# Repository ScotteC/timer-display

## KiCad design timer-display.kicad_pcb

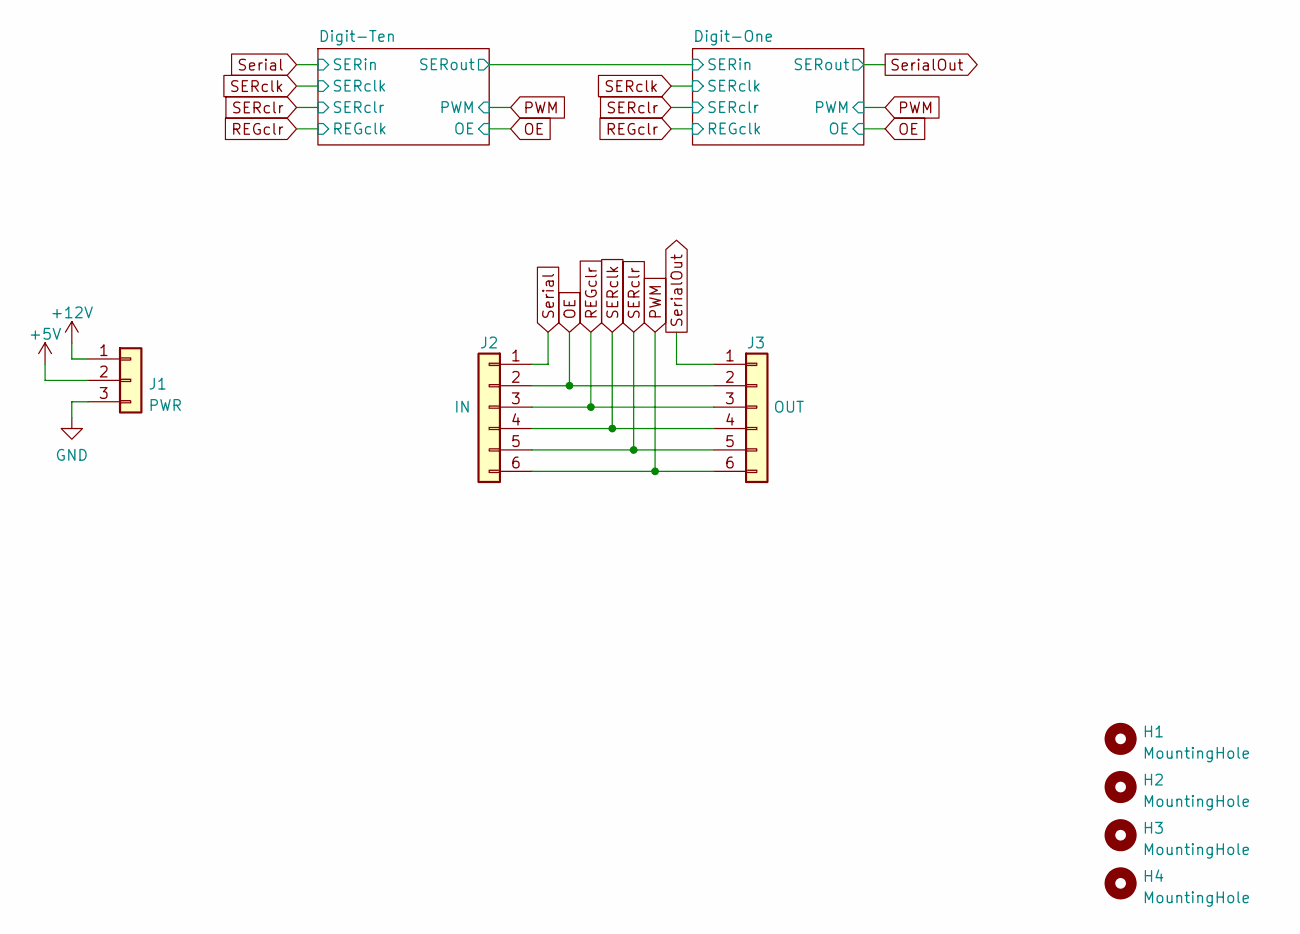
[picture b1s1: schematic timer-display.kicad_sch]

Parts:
H1, H2, H3, H4: MountingHole; MountingHole_3.2mm_M3
J1: PWR; PinSocket_1x03_P2.54mm_Vertical
J2: IN; PinSocket_1x06_P1.27mm_Vertical
J3: OUT; PinSocket_1x06_P1.27mm_Vertical

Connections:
+5V: J1.2; also elsewhere on the board
+12V: J1.1; also elsewhere on the board
GND: J1.3; also elsewhere on the board
OE: J2.2, J3.2; also elsewhere on the board
PWM: J2.6, J3.6; also elsewhere on the board
REGclr: J2.3, J3.3; also elsewhere on the board
SERclk: J2.4, J3.4; also elsewhere on the board
SERclr: J2.5, J3.5; also elsewhere on the board
Serial: J2.1; also elsewhere on the board
SerialOut: J3.1; also elsewhere on the board

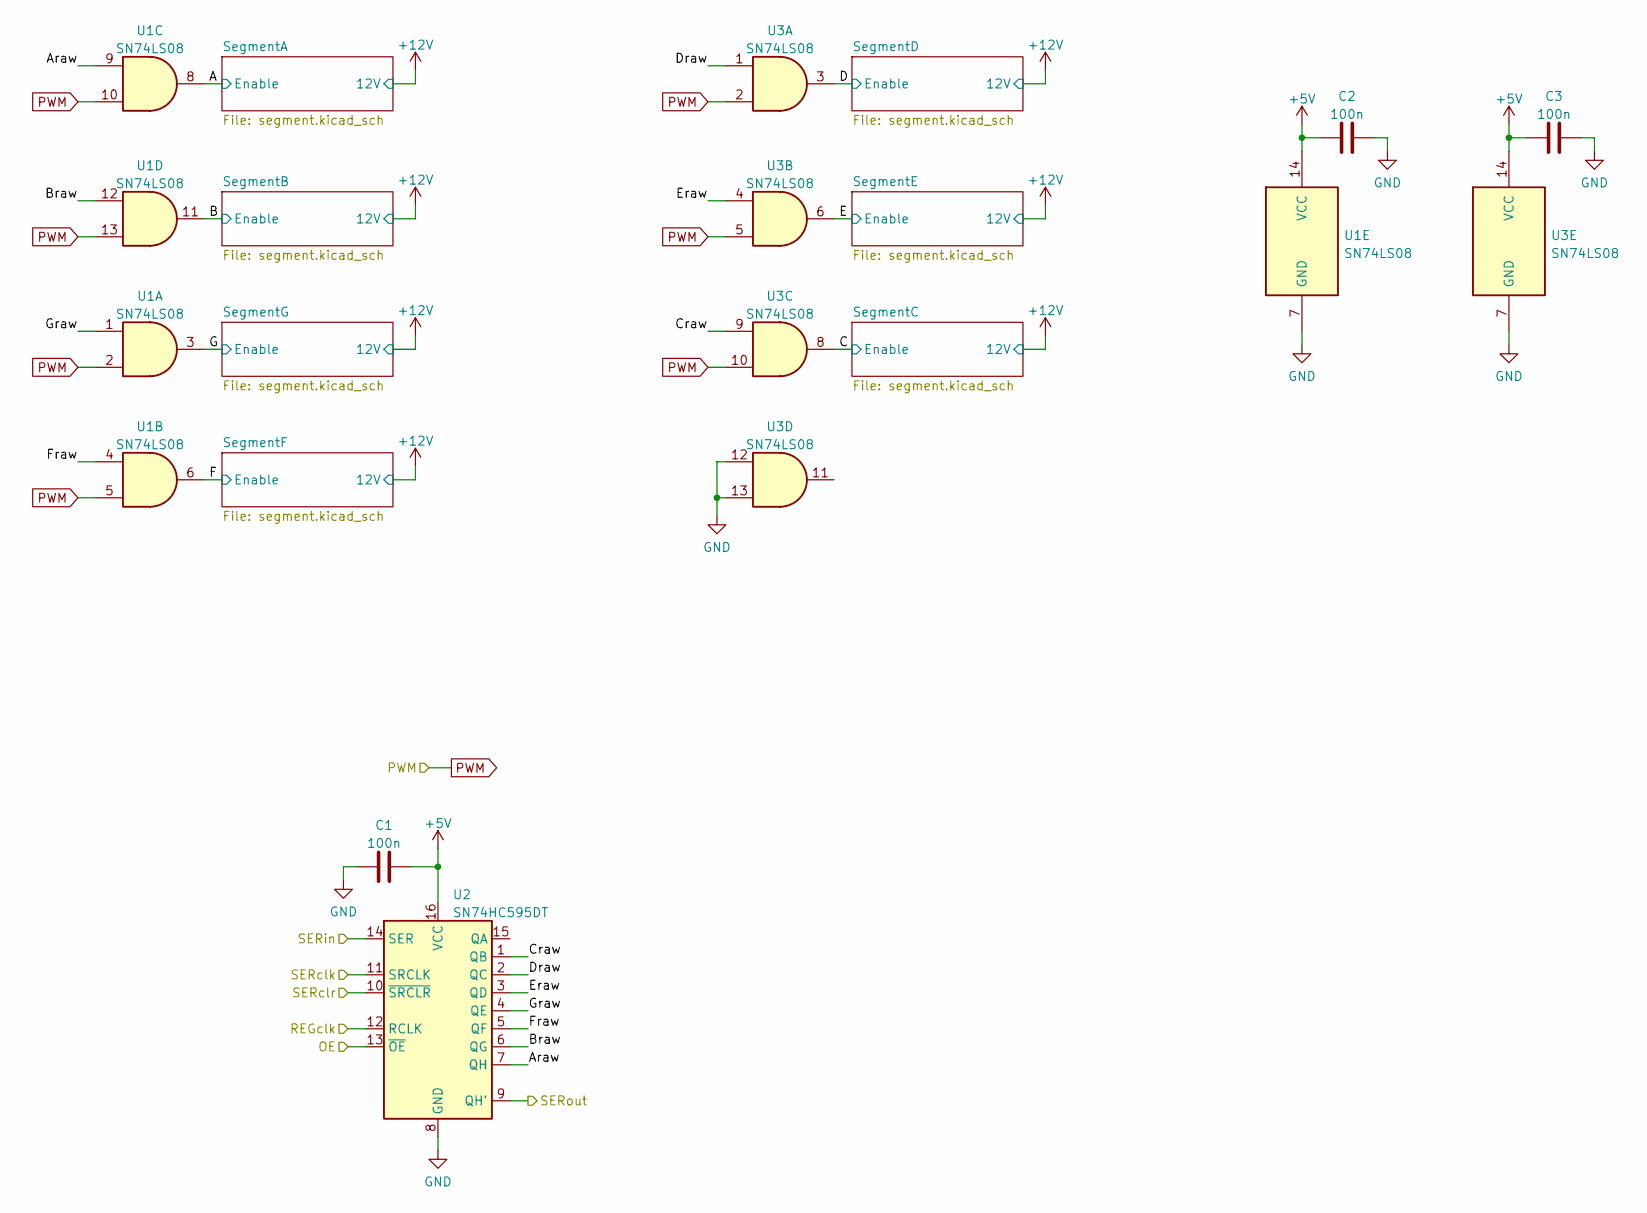
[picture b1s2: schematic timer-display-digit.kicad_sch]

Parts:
C1, C2, C3: 100n; C_0603_1608Metric
U1, U3: SN74LS08; SOIC-14_3.9x8.7mm_P1.27mm; Mouser# 595-SN74LS08DR
U2: SN74HC595DT; SOIC-16_3.9x9.9mm_P1.27mm; Mouser# 595-SN74HC595DT

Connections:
+5V: C1.1, C2.1, C3.1, U1.14 (VCC), U2.16 (VCC), U3.14 (VCC); also elsewhere on the board
/Digit-One/SERin: U2.9 (QH'); also elsewhere on the board
/Digit-Ten/A: U1.8; also elsewhere on the board
/Digit-Ten/Araw: U1.9, U2.7 (QH)
/Digit-Ten/B: U1.11; also elsewhere on the board
/Digit-Ten/Braw: U1.12, U2.6 (QG)
/Digit-Ten/C: U3.8; also elsewhere on the board
/Digit-Ten/Craw: U2.1 (QB), U3.9
/Digit-Ten/D: U3.3; also elsewhere on the board
/Digit-Ten/Draw: U2.2 (QC), U3.1
/Digit-Ten/E: U3.6; also elsewhere on the board
/Digit-Ten/Eraw: U2.3 (QD), U3.4
/Digit-Ten/F: U1.6; also elsewhere on the board
/Digit-Ten/Fraw: U1.4, U2.5 (QF)
/Digit-Ten/G: U1.3; also elsewhere on the board
/Digit-Ten/Graw: U1.1, U2.4 (QE)
GND: C1.2, C2.2, C3.2, U1.7 (GND), U2.8 (GND), U3.7 (GND), U3.12, U3.13; also elsewhere on the board
OE: U2.13 (~OE); also elsewhere on the board
PWM: U1.2, U1.5, U1.10, U1.13, U3.2, U3.5, U3.10; also elsewhere on the board
REGclr: U2.12 (RCLK); also elsewhere on the board
SERclk: U2.11 (SRCLK); also elsewhere on the board
SERclr: U2.10 (~SRCLR); also elsewhere on the board
Serial: U2.14 (SER); also elsewhere on the board

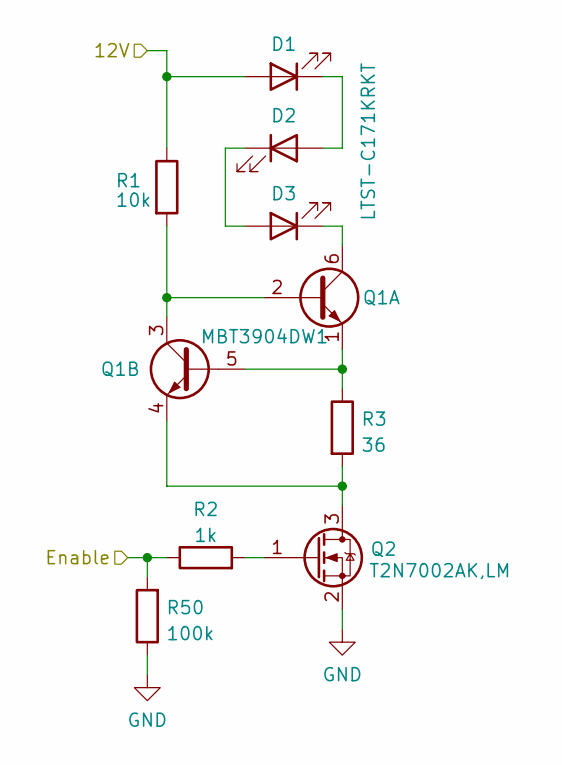
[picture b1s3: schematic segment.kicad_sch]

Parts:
D1, D2, D3: LTST-C171KRKT; LED_0805_2012Metric; Mouser# 859-LTST-C171KRKT
Q1: MBT3904DW1; SOT-363_SC-70-6; Mouser# 863-MBT3904DW1T3G
Q2: T2N7002AK,LM; SOT-23; Mouser# 757-T2N7002AKLM
R1: 10k; R_0603_1608Metric
R2: 1k; R_0603_1608Metric; Mouser# 791-RMC1/16-100JTP
R3: 36; R_0603_1608Metric; Mouser# 603-RC0603FR-0736RL
R50: 100k; R_0603_1608Metric; Mouser# 791-RMC1/16-100JTP

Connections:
+12V: D1.2 (A), R1.1; also elsewhere on the board
/Digit-Ten/A: R2.1, R50.2; also elsewhere on the board
GND: Q2.2 (S), R50.1; also elsewhere on the board
unnamed: D1.1 (K), D2.2 (A)
unnamed: D2.1 (K), D3.2 (A)
unnamed: D3.1 (K), Q1.6 (C1)
unnamed: Q1.1 (E1), Q1.5 (B2), R3.1
unnamed: Q1.2 (B1), Q1.3 (C2), R1.2
unnamed: Q1.4 (E2), Q2.3 (D), R3.2
unnamed: Q2.1 (G), R2.2

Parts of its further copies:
D4, D5, D6, D7, D8, D9, D10, D11, D12, D13, D14, D15, D16, D17, D18, D19, D20, D21, D22, D23, D24, D25, D26, D27, D28, D29, D30, D31, D32, D33, D34, D35, D36, D37, D38, D39, D40, D41, D42: LTST-C171KRKT; LED_0805_2012Metric; Mouser# 859-LTST-C171KRKT
Q3, Q5, Q7, Q9, Q11, Q13, Q15, Q17, Q19, Q21, Q23, Q25, Q27: MBT3904DW1; SOT-363_SC-70-6; Mouser# 863-MBT3904DW1T3G
Q4, Q6, Q8, Q10, Q12, Q14, Q16, Q18, Q20, Q22, Q24, Q26, Q28: T2N7002AK,LM; SOT-23; Mouser# 757-T2N7002AKLM
R4, R7, R10, R13, R16, R19, R22, R25, R28, R31, R34, R37, R40: 10k; R_0603_1608Metric
R5, R8, R11, R14, R17, R20, R23, R26, R29, R32, R35, R38, R41: 1k; R_0603_1608Metric; Mouser# 791-RMC1/16-100JTP
R6, R9, R12, R15, R18, R21, R24, R27, R30, R33, R36, R39, R42: 36; R_0603_1608Metric; Mouser# 603-RC0603FR-0736RL
R43, R44, R45, R46, R47, R48, R49, R51, R52, R53, R54, R55, R56: 100k; R_0603_1608Metric; Mouser# 791-RMC1/16-100JTP

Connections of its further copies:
+12V: D4.2 (A), D7.2 (A), D10.2 (A), D13.2 (A), D16.2 (A), D19.2 (A), D22.2 (A), D25.2 (A), D28.2 (A), D31.2 (A), D34.2 (A), D37.2 (A), D40.2 (A), R4.1, R7.1, R10.1, R13.1, R16.1, R19.1, R22.1, R25.1, R28.1, R31.1, R34.1, R37.1, R40.1; also elsewhere on the board
/Digit-One/A: R29.1, R45.2; also elsewhere on the board
/Digit-One/B: R32.1, R46.2; also elsewhere on the board
/Digit-One/C: R38.1, R48.2; also elsewhere on the board
/Digit-One/D: R35.1, R47.2; also elsewhere on the board
/Digit-One/E: R41.1, R49.2; also elsewhere on the board
/Digit-One/F: R23.1, R43.2; also elsewhere on the board
/Digit-One/G: R26.1, R44.2; also elsewhere on the board
/Digit-Ten/B: R5.1, R51.2; also elsewhere on the board
/Digit-Ten/C: R8.1, R56.2; also elsewhere on the board
/Digit-Ten/D: R11.1, R54.2; also elsewhere on the board
/Digit-Ten/E: R14.1, R55.2; also elsewhere on the board
/Digit-Ten/F: R17.1, R53.2; also elsewhere on the board
/Digit-Ten/G: R20.1, R52.2; also elsewhere on the board
GND: Q4.2 (S), Q6.2 (S), Q8.2 (S), Q10.2 (S), Q12.2 (S), Q14.2 (S), Q16.2 (S), Q18.2 (S), Q20.2 (S), Q22.2 (S), Q24.2 (S), Q26.2 (S), Q28.2 (S), R43.1, R44.1, R45.1, R46.1, R47.1, R48.1, R49.1, R51.1, R52.1, R53.1, R54.1, R55.1, R56.1; also elsewhere on the board
unnamed: D4.1 (K), D5.2 (A)
unnamed: D5.1 (K), D6.2 (A)
unnamed: D6.1 (K), Q3.6 (C1)
unnamed: D7.1 (K), D8.2 (A)
unnamed: D8.1 (K), D9.2 (A)
unnamed: D9.1 (K), Q5.6 (C1)
unnamed: D10.1 (K), D11.2 (A)
unnamed: D11.1 (K), D12.2 (A)
unnamed: D12.1 (K), Q7.6 (C1)
unnamed: D13.1 (K), D14.2 (A)
unnamed: D14.1 (K), D15.2 (A)
unnamed: D15.1 (K), Q9.6 (C1)
unnamed: D16.1 (K), D17.2 (A)
unnamed: D17.1 (K), D18.2 (A)
unnamed: D18.1 (K), Q11.6 (C1)
unnamed: D19.1 (K), D20.2 (A)
unnamed: D20.1 (K), D21.2 (A)
unnamed: D21.1 (K), Q13.6 (C1)
unnamed: D22.1 (K), D23.2 (A)
unnamed: D23.1 (K), D24.2 (A)
unnamed: D24.1 (K), Q15.6 (C1)
unnamed: D25.1 (K), D26.2 (A)
unnamed: D26.1 (K), D27.2 (A)
unnamed: D27.1 (K), Q17.6 (C1)
unnamed: D28.1 (K), D29.2 (A)
unnamed: D29.1 (K), D30.2 (A)
unnamed: D30.1 (K), Q19.6 (C1)
unnamed: D31.1 (K), D32.2 (A)
unnamed: D32.1 (K), D33.2 (A)
unnamed: D33.1 (K), Q21.6 (C1)
unnamed: D34.1 (K), D35.2 (A)
unnamed: D35.1 (K), D36.2 (A)
unnamed: D36.1 (K), Q23.6 (C1)
unnamed: D37.1 (K), D38.2 (A)
unnamed: D38.1 (K), D39.2 (A)
unnamed: D39.1 (K), Q25.6 (C1)
unnamed: D40.1 (K), D41.2 (A)
unnamed: D41.1 (K), D42.2 (A)
unnamed: D42.1 (K), Q27.6 (C1)
unnamed: Q3.1 (E1), Q3.5 (B2), R6.1
unnamed: Q3.2 (B1), Q3.3 (C2), R4.2
unnamed: Q3.4 (E2), Q4.3 (D), R6.2
unnamed: Q4.1 (G), R5.2
unnamed: Q5.1 (E1), Q5.5 (B2), R9.1
unnamed: Q5.2 (B1), Q5.3 (C2), R7.2
unnamed: Q5.4 (E2), Q6.3 (D), R9.2
unnamed: Q6.1 (G), R8.2
unnamed: Q7.1 (E1), Q7.5 (B2), R12.1
unnamed: Q7.2 (B1), Q7.3 (C2), R10.2
unnamed: Q7.4 (E2), Q8.3 (D), R12.2
unnamed: Q8.1 (G), R11.2
unnamed: Q9.1 (E1), Q9.5 (B2), R15.1
unnamed: Q9.2 (B1), Q9.3 (C2), R13.2
unnamed: Q10.1 (G), R14.2
unnamed: Q9.4 (E2), Q10.3 (D), R15.2
unnamed: Q11.1 (E1), Q11.5 (B2), R18.1
unnamed: Q11.2 (B1), Q11.3 (C2), R16.2
unnamed: Q11.4 (E2), Q12.3 (D), R18.2
unnamed: Q12.1 (G), R17.2
unnamed: Q13.1 (E1), Q13.5 (B2), R21.1
unnamed: Q13.2 (B1), Q13.3 (C2), R19.2
unnamed: Q13.4 (E2), Q14.3 (D), R21.2
unnamed: Q14.1 (G), R20.2
unnamed: Q15.1 (E1), Q15.5 (B2), R24.1
unnamed: Q15.2 (B1), Q15.3 (C2), R22.2
unnamed: Q15.4 (E2), Q16.3 (D), R24.2
unnamed: Q16.1 (G), R23.2
unnamed: Q17.1 (E1), Q17.5 (B2), R27.1
unnamed: Q17.2 (B1), Q17.3 (C2), R25.2
unnamed: Q17.4 (E2), Q18.3 (D), R27.2
unnamed: Q18.1 (G), R26.2
unnamed: Q19.1 (E1), Q19.5 (B2), R30.1
unnamed: Q19.2 (B1), Q19.3 (C2), R28.2
unnamed: Q19.4 (E2), Q20.3 (D), R30.2
unnamed: Q20.1 (G), R29.2
unnamed: Q21.1 (E1), Q21.5 (B2), R33.1
unnamed: Q21.2 (B1), Q21.3 (C2), R31.2
unnamed: Q21.4 (E2), Q22.3 (D), R33.2
unnamed: Q22.1 (G), R32.2
unnamed: Q23.1 (E1), Q23.5 (B2), R36.1
unnamed: Q23.2 (B1), Q23.3 (C2), R34.2
unnamed: Q23.4 (E2), Q24.3 (D), R36.2
unnamed: Q24.1 (G), R35.2
unnamed: Q25.1 (E1), Q25.5 (B2), R39.1
unnamed: Q25.2 (B1), Q25.3 (C2), R37.2
unnamed: Q25.4 (E2), Q26.3 (D), R39.2
unnamed: Q26.1 (G), R38.2
unnamed: Q27.1 (E1), Q27.5 (B2), R42.1
unnamed: Q27.2 (B1), Q27.3 (C2), R40.2
unnamed: Q27.4 (E2), Q28.3 (D), R42.2
unnamed: Q28.1 (G), R41.2

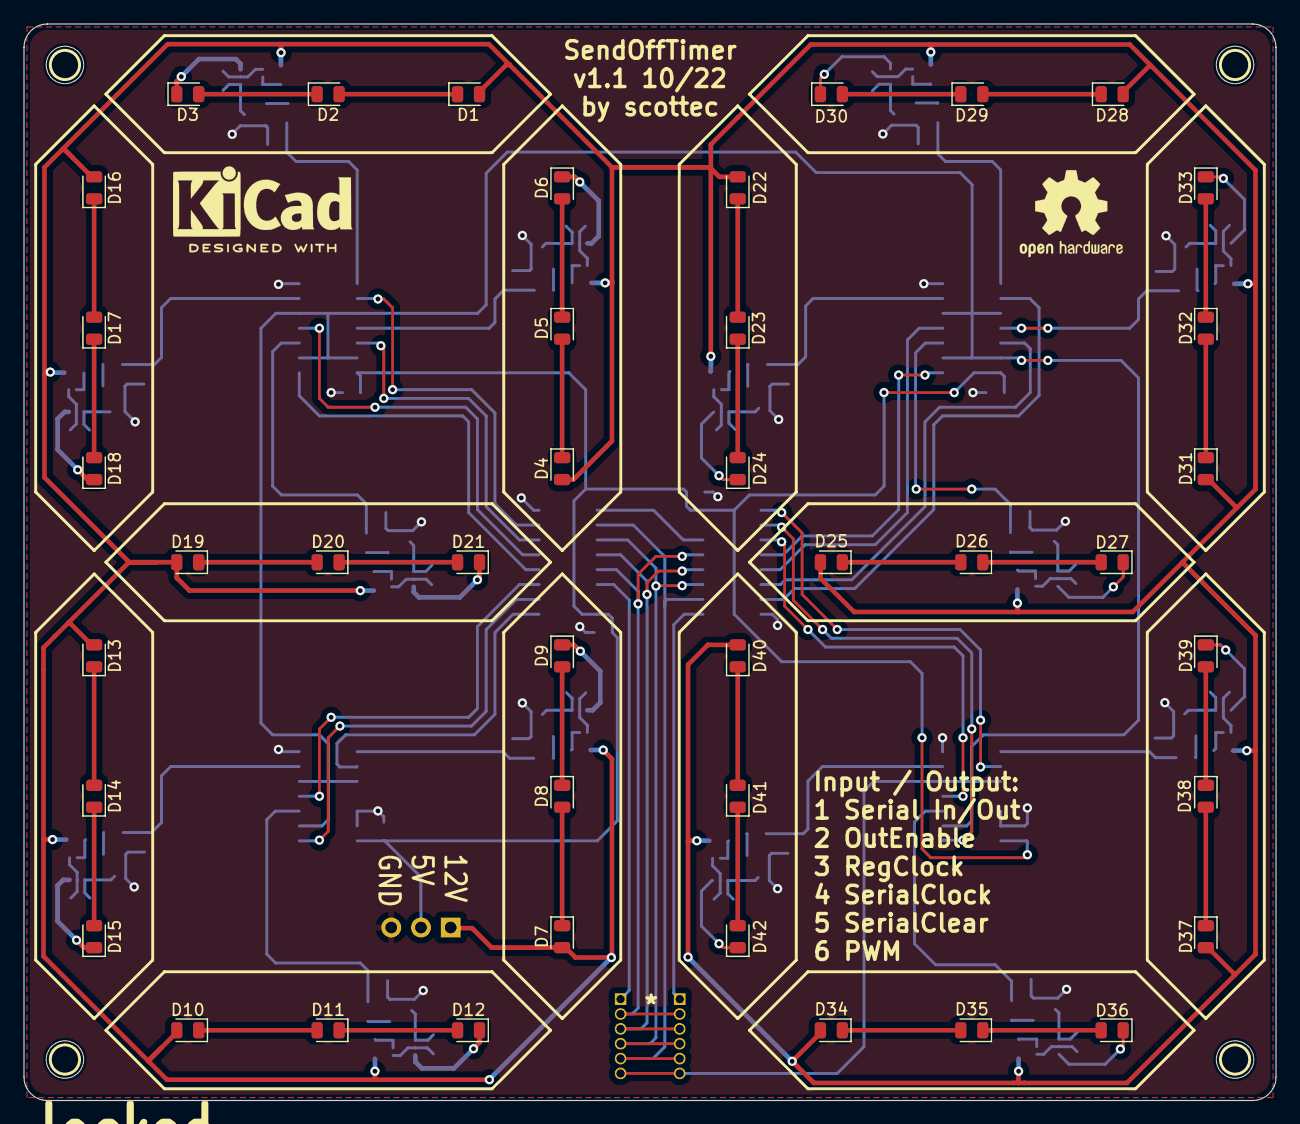
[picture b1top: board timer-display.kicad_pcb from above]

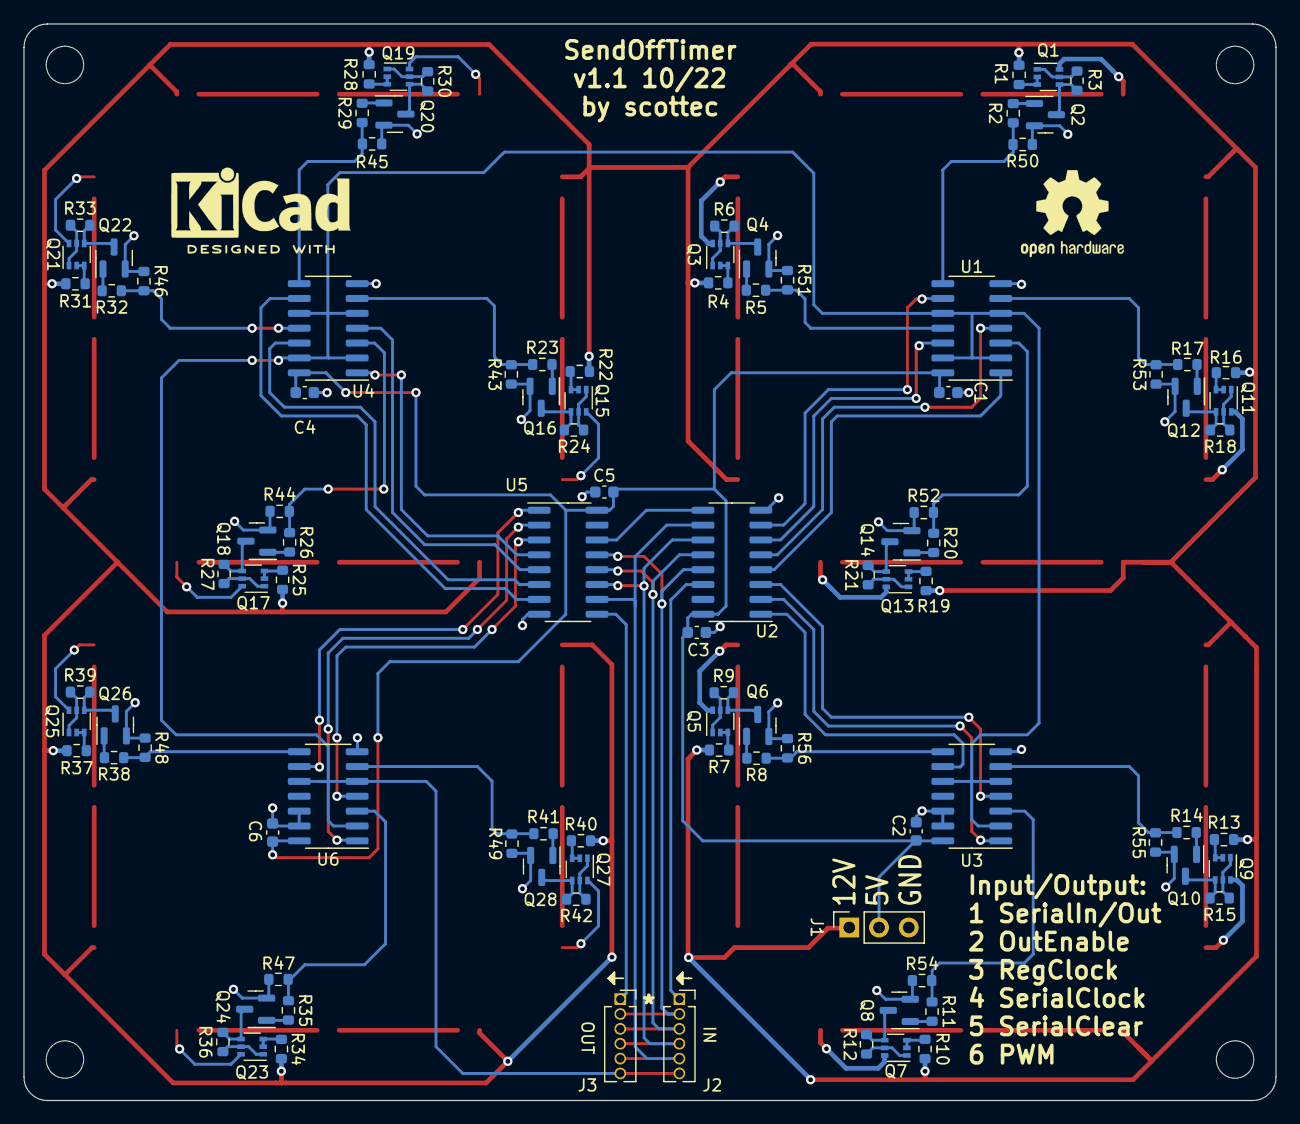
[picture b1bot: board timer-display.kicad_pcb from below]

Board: 2 copper layers, 107.0 x 92.0 mm, 145 parts (99 on the bottom side), 137 nets.

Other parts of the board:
C4, C5, C6: 100n; C_0603_1608Metric
U4, U6: SN74LS08; SOIC-14_3.9x8.7mm_P1.27mm
U5: SN74HC595DT; SOIC-16_3.9x9.9mm_P1.27mm

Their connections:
+5V: C4.1, C5.1, C6.1, U4.14 (VCC), U5.16 (VCC), U6.14 (VCC); also elsewhere on the board
/Digit-One/A: U4.8; also elsewhere on the board
/Digit-One/Araw: U4.9, U5.7 (QH)
/Digit-One/B: U4.11; also elsewhere on the board
/Digit-One/Braw: U4.12, U5.6 (QG)
/Digit-One/C: U6.8; also elsewhere on the board
/Digit-One/Craw: U5.1 (QB), U6.9
/Digit-One/D: U6.3; also elsewhere on the board
/Digit-One/Draw: U5.2 (QC), U6.1
/Digit-One/E: U6.6; also elsewhere on the board
/Digit-One/Eraw: U5.3 (QD), U6.4
/Digit-One/F: U4.6; also elsewhere on the board
/Digit-One/Fraw: U4.4, U5.5 (QF)
/Digit-One/G: U4.3; also elsewhere on the board
/Digit-One/Graw: U4.1, U5.4 (QE)
/Digit-One/SERin: U5.14 (SER); also elsewhere on the board
GND: C4.2, C5.2, C6.2, U4.7 (GND), U5.8 (GND), U6.7 (GND), U6.12, U6.13; also elsewhere on the board
OE: U5.13 (~OE); also elsewhere on the board
PWM: U4.2, U4.5, U4.10, U4.13, U6.2, U6.5, U6.10; also elsewhere on the board
REGclr: U5.12 (RCLK); also elsewhere on the board
SERclk: U5.11 (SRCLK); also elsewhere on the board
SERclr: U5.10 (~SRCLR); also elsewhere on the board
SerialOut: U5.9 (QH'); also elsewhere on the board

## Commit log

2022-10-02 first half done
2023-08-16 production ready
2024-02-21 7.0.1 -> 7.0.10
